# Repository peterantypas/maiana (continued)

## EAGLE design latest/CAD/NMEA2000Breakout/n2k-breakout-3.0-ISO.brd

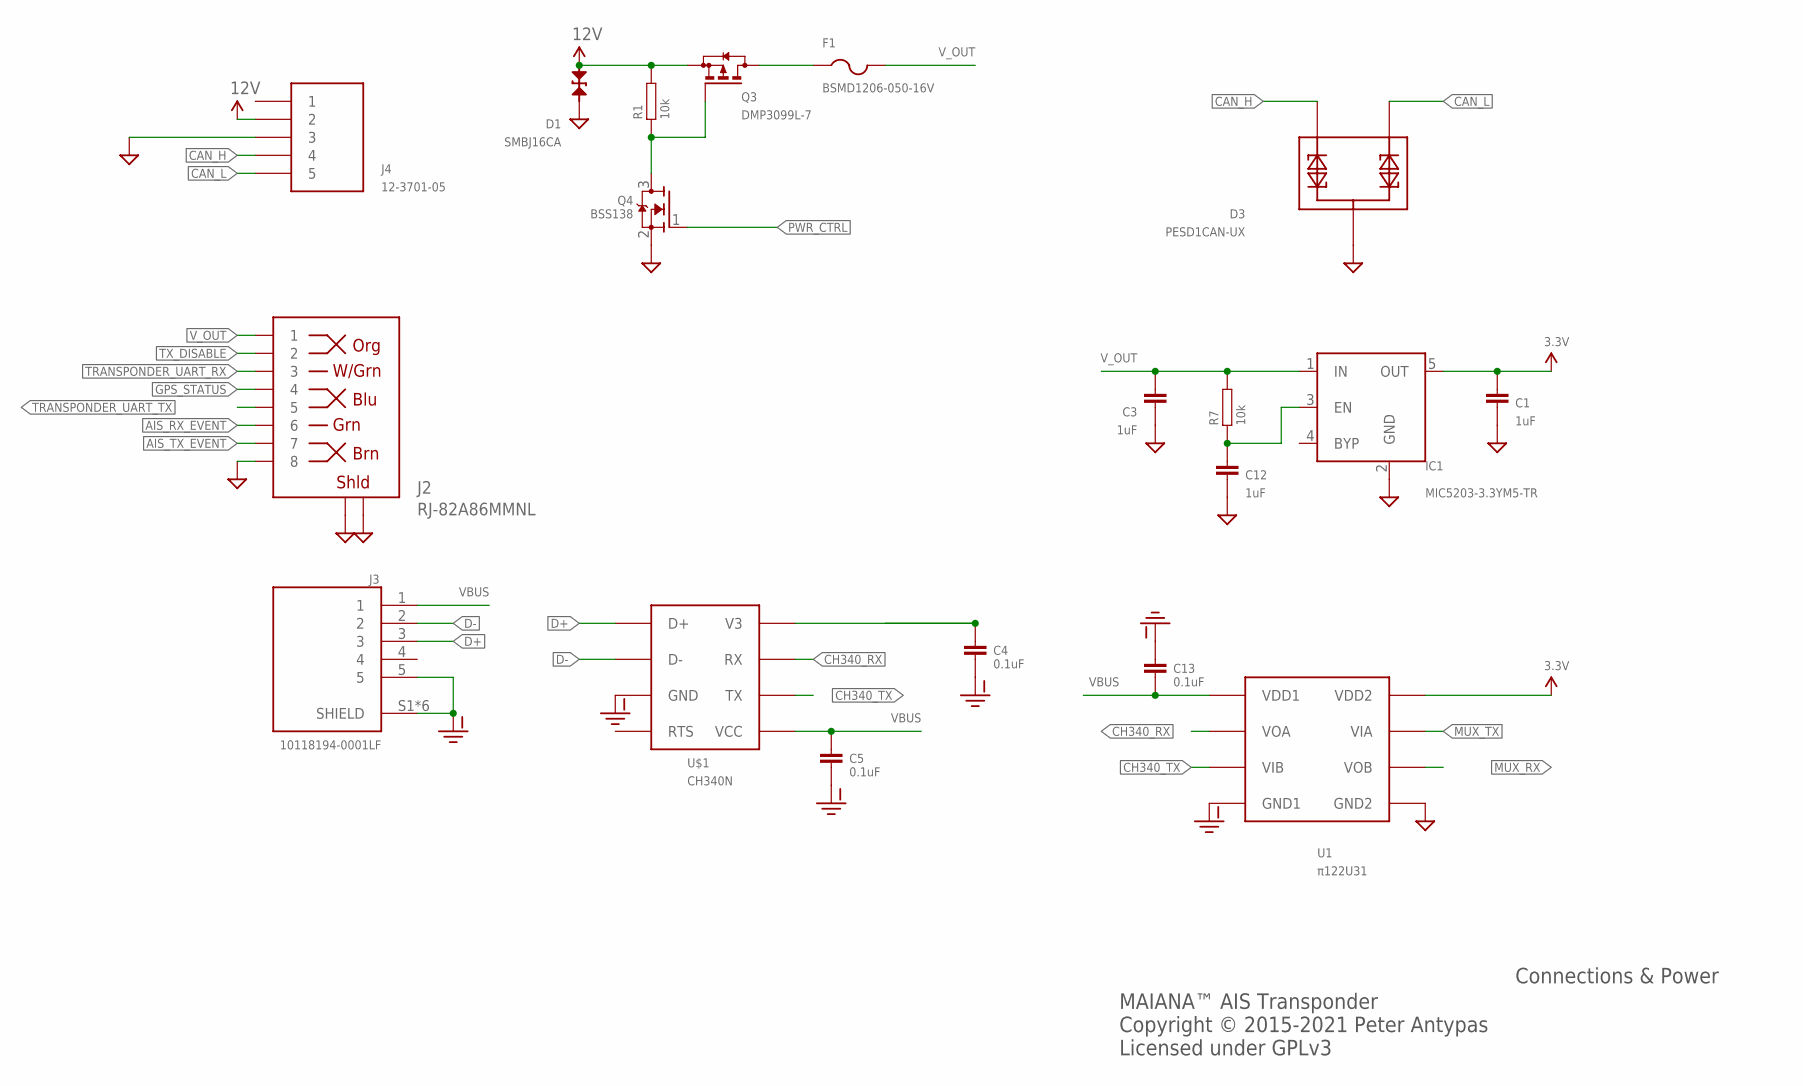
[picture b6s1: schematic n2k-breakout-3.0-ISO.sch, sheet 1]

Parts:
C1, C3, C12: 1uF; 0603
C4, C5, C13: 0.1uF; 0603
D1: SMBJ16CA; SMB-BIDIR
D3: PESD1CAN-UX; SOT65P210X110-3N
F1: BSMD1206-050-16V; R1206
IC1: MIC5203-3.3YM5-TR; SOT23-5
J2: RJ-82A86MMNL
J3: 10118194-0001LF; AMPHENOL_10118194-0001LF
J4: 12-3701-05; MICRO_C_5PIN
Q3: DMP3099L-7; SOT23
Q4: BSS138; SOT23
R1, R7: 10k; 0603
U1: π122U31; SOIC8; PARTNO π122U31
U$1: CH340N; SOIC-8; PARTNO CH340N

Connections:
3.3V: C1.P$1 (1), IC1.5 (OUT), U1.8 (VDD2); also elsewhere on the board
12V: D1.A, J4.2, Q3.2 (S), R1.P$2; also elsewhere on the board
AIS_RX_EVENT: J2.P$6 (6); also elsewhere on the board
AIS_TX_EVENT: J2.P$7 (7); also elsewhere on the board
CAN_H: D3.2, J4.4; also elsewhere on the board
CAN_L: D3.1, J4.5; also elsewhere on the board
CH340_RX: U1.2 (VOA), U$1.7 (RX)
CH340_TX: U1.3 (VIB), U$1.6 (TX)
D+: J3.3, U$1.1 (D+)
D-: J3.2, U$1.2 (D-)
GND: C1.P$2 (2), C3.P$2 (2), C12.P$2 (2), D1.C, D3.3, IC1.2 (GND), J2.P$8 (8), J2.P$9 (SHLD), J2.P$10 (SHLD), J2.P$11 (SHLD), J2.P$12 (SHLD), J4.3, Q4.2 (S), U1.5 (GND2); also elsewhere on the board
GND-ISO: C4.P$2 (2), C5.P$2 (2), C13.P$1 (1), J3.5, J3.S1 (SHIELD), J3.S2 (SHIELD), J3.S3 (SHIELD), J3.S4 (SHIELD), J3.S5 (SHIELD), J3.S6 (SHIELD), U1.4 (GND1), U$1.3 (GND)
GPS_STATUS: J2.P$4 (4); also elsewhere on the board
MUX_RX: U1.6 (VOB); also elsewhere on the board
MUX_TX: U1.7 (VIA); also elsewhere on the board
unnamed: C4.P$1 (1), U$1.8 (V3)
unnamed: Q3.1 (G), Q4.3 (D), R1.P$1
unnamed: C12.P$1 (1), IC1.3 (EN), R7.P$1
unnamed: F1.1, Q3.3 (D)
PWR_CTRL: Q4.1 (G); also elsewhere on the board
TRANSPONDER_UART_RX: J2.P$3 (3); also elsewhere on the board
TRANSPONDER_UART_TX: J2.P$5 (5); also elsewhere on the board
TX_DISABLE: J2.P$2 (2); also elsewhere on the board
VBUS: C5.P$1 (1), C13.P$2 (2), J3.1, U1.1 (VDD1), U$1.5 (VCC)
V_OUT: C3.P$1 (1), F1.2, IC1.1 (IN), J2.P$1 (1), R7.P$2

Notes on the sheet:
MAIANA™ AIS Transponder Copyright © 2015-2021 Peter Antypas Licensed under GPLv3
Connections & Power

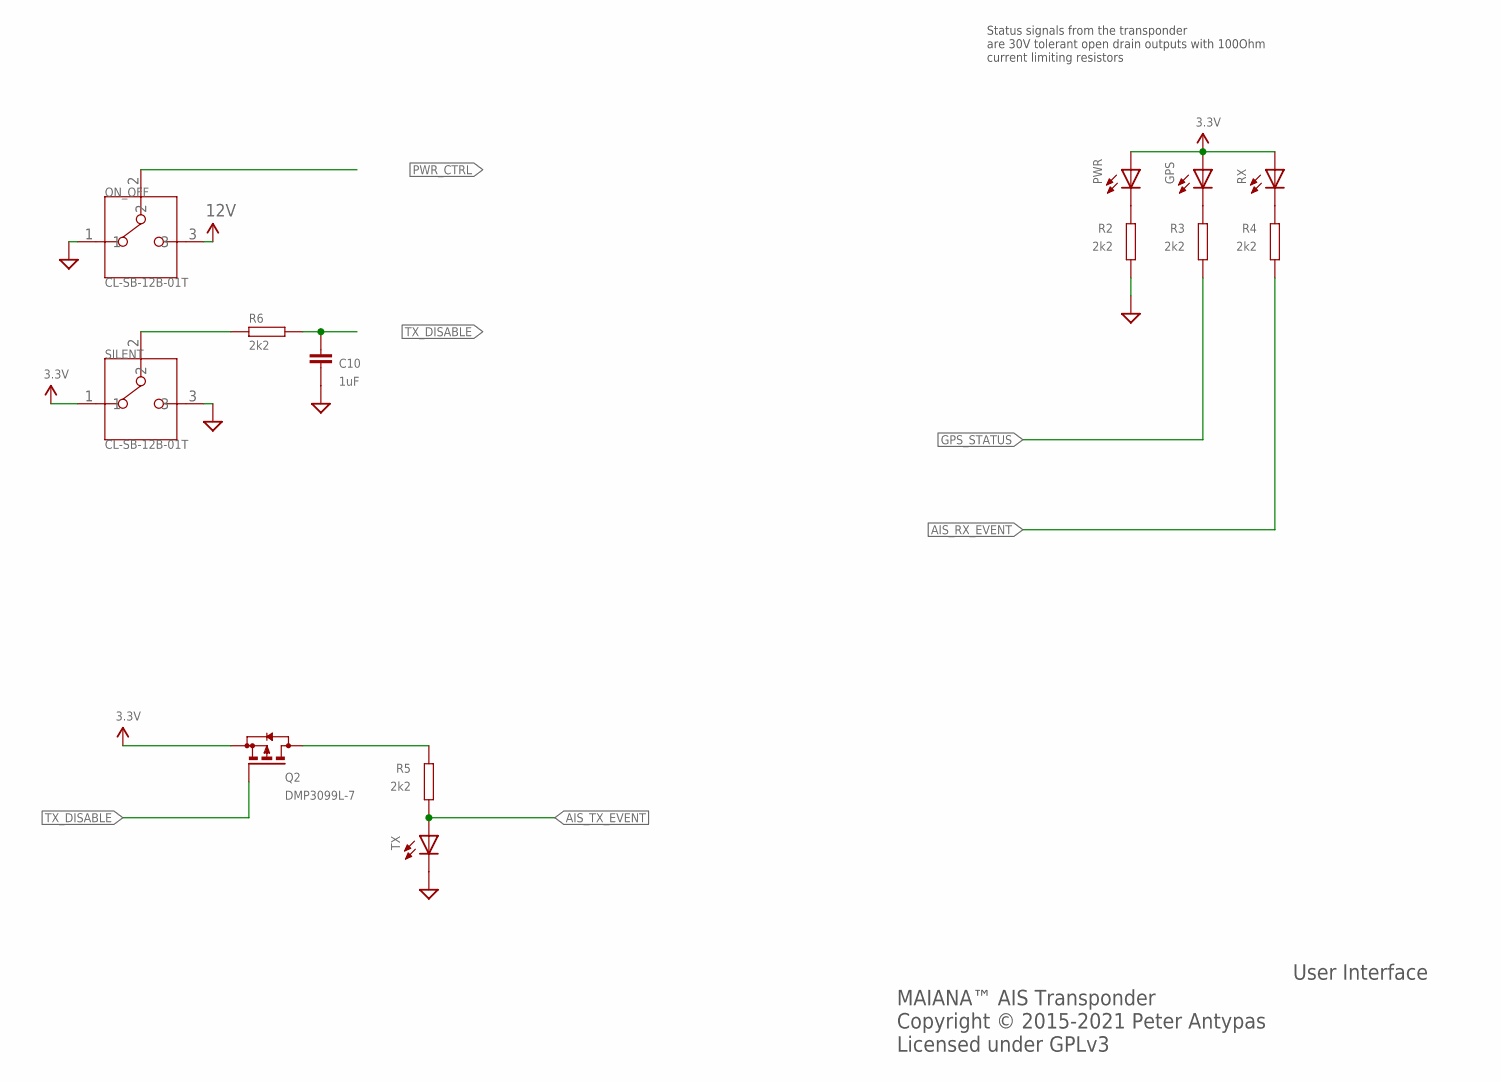
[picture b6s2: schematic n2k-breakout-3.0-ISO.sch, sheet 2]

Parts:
C10: 1uF; 0603
GPS: LEDCHIPLED_1206; CHIPLED_1206; PARTNO TJ-S3216CL9T5ALC2G-A5
ON_OFF: CL-SB-12B-01T; CL-SB-12B
PWR: LEDCHIPLED_1206; CHIPLED_1206; PARTNO TJ-S3216CL9T5ALC2G-A5
Q2: DMP3099L-7; SOT23
R2, R3, R4, R5, R6: 2k2; 0603
RX: LEDCHIPLED_1206; CHIPLED_1206; PARTNO TJ-S3216CL9T5ALC2G-A5
SILENT: CL-SB-12B-01T; CL-SB-12B
TX: LEDCHIPLED_1206; CHIPLED_1206; PARTNO TJ-S3216CL9T5ALC2G-A5

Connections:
3.3V: GPS.A, PWR.A, Q2.2 (S), RX.A, SILENT.1; also elsewhere on the board
12V: ON_OFF.3; also elsewhere on the board
AIS_RX_EVENT: R4.P$2; also elsewhere on the board
AIS_TX_EVENT: R5.P$2, TX.A; also elsewhere on the board
GND: C10.P$2 (2), ON_OFF.1, R2.P$2, SILENT.3, TX.C; also elsewhere on the board
GPS_STATUS: R3.P$2; also elsewhere on the board
unnamed: PWR.C, R2.P$1
unnamed: GPS.C, R3.P$1
unnamed: R4.P$1, RX.C
unnamed: R6.P$1, SILENT.2
unnamed: Q2.3 (D), R5.P$1
PWR_CTRL: ON_OFF.2; also elsewhere on the board
TX_DISABLE: C10.P$1 (1), Q2.1 (G), R6.P$2; also elsewhere on the board

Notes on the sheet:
Status signals from the transponder are 30V tolerant open drain outputs with 100Ohm current limiting resistors
MAIANA™ AIS Transponder Copyright © 2015-2021 Peter Antypas Licensed under GPLv3
User Interface

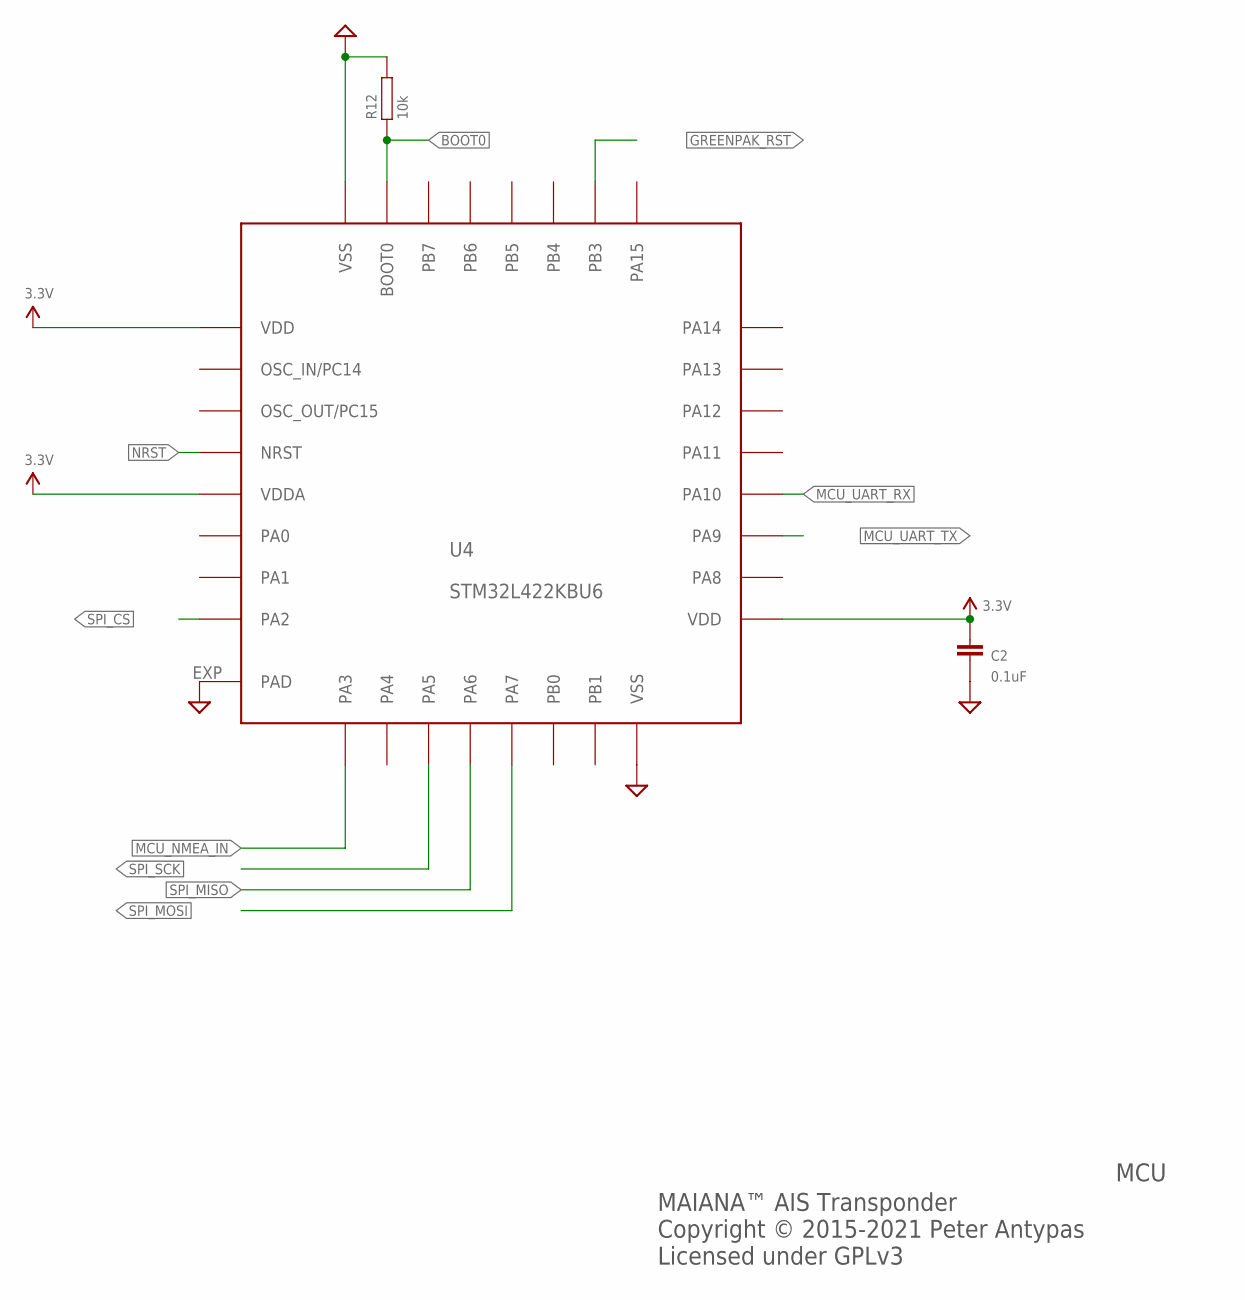
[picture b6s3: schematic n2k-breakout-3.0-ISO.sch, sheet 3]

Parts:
C2: 0.1uF; 0603
R12: 10k; 0603
U4: STM32L422KBU6; QFN32

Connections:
3.3V: C2.P$1 (1), U4.1 (VDD), U4.5 (VDDA), U4.17 (VDD); also elsewhere on the board
BOOT0: R12.P$1, U4.31 (BOOT0); also elsewhere on the board
GND: C2.P$2 (2), R12.P$2, U4.16 (VSS), U4.32 (VSS), U4.EXP (PAD); also elsewhere on the board
GREENPAK_RST: U4.26 (PB3); also elsewhere on the board
MCU_NMEA_IN: U4.9 (PA3); also elsewhere on the board
MCU_UART_RX: U4.20 (PA10); also elsewhere on the board
MCU_UART_TX: U4.19 (PA9); also elsewhere on the board
NRST: U4.4 (NRST); also elsewhere on the board
SPI_CS: U4.8 (PA2); also elsewhere on the board
SPI_MISO: U4.12 (PA6); also elsewhere on the board
SPI_MOSI: U4.13 (PA7); also elsewhere on the board
SPI_SCK: U4.11 (PA5); also elsewhere on the board

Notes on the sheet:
MAIANA™ AIS Transponder Copyright © 2015-2021 Peter Antypas Licensed under GPLv3
MCU

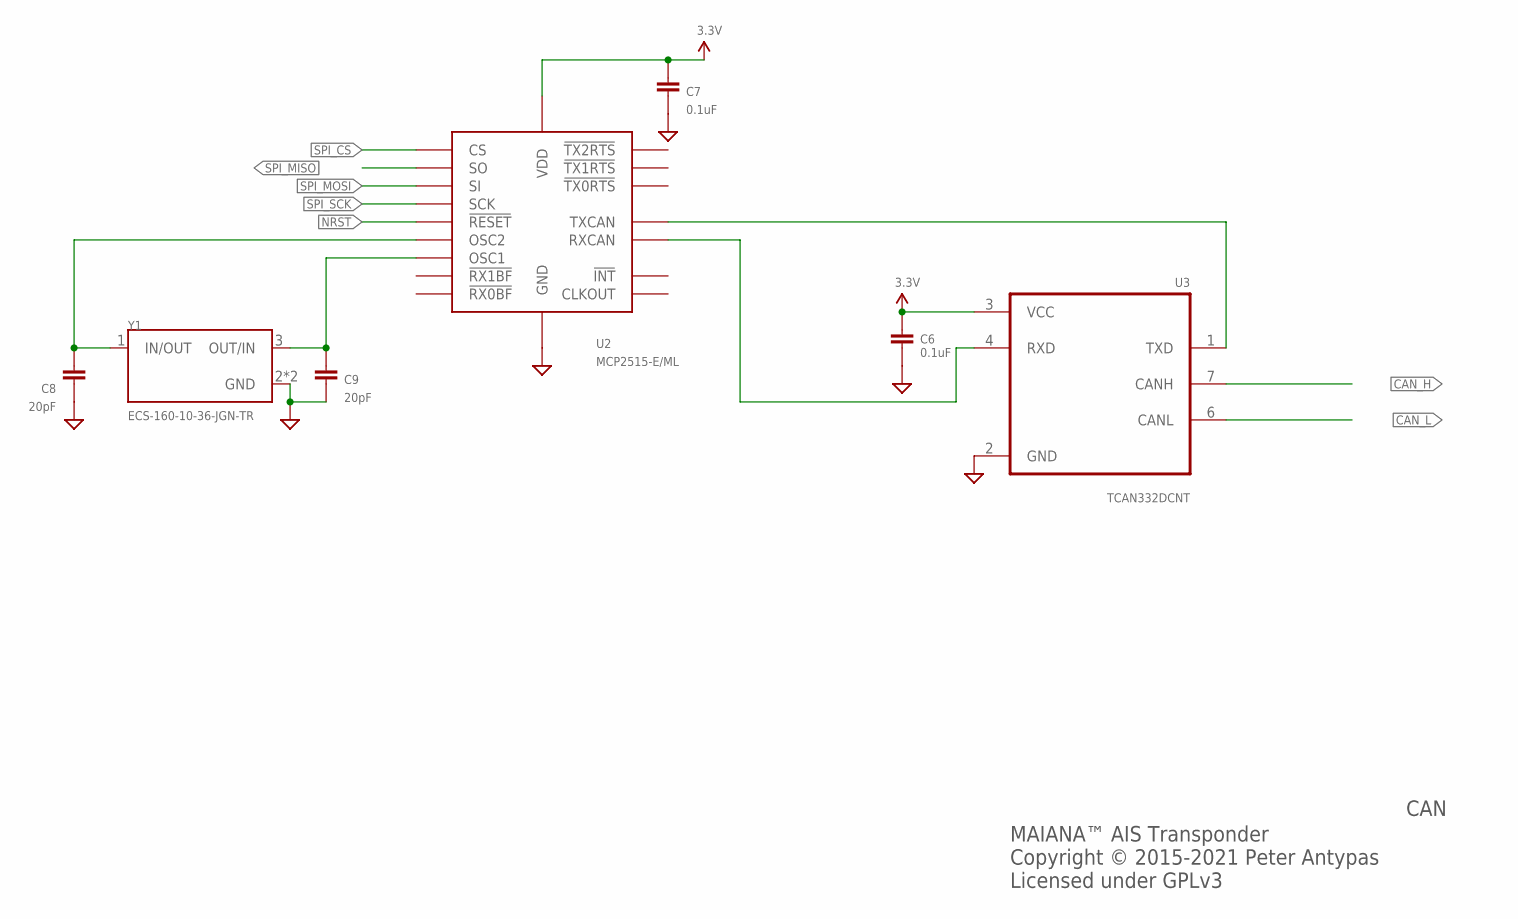
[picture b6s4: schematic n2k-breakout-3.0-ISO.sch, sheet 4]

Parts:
C6, C7: 0.1uF; 0603
C8, C9: 20pF; 0603
U2: MCP2515-E/ML; QFN20-4X4
U3: TCAN332DCNT; SOT65P280X145-8N; PARTNO TCAN332DCNT
Y1: ECS-160-10-36-JGN-TR; XTAL_ECS-160-10-36-JGN-TR

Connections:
3.3V: C6.P$1 (1), C7.P$1 (1), U2.18 (VDD), U3.3 (VCC); also elsewhere on the board
CAN_H: U3.7 (CANH); also elsewhere on the board
CAN_L: U3.6 (CANL); also elsewhere on the board
GND: C6.P$2 (2), C7.P$2 (2), C8.P$2 (2), C9.P$2 (2), U2.8 (GND), U2.EXP (GND), U3.2 (GND), Y1.2 (GND), Y1.4 (GND); also elsewhere on the board
unnamed: U2.20 (RXCAN), U3.4 (RXD)
unnamed: U2.19 (TXCAN), U3.1 (TXD)
unnamed: C9.P$1 (1), U2.7 (OSC1), Y1.3 (OUT/IN)
unnamed: C8.P$1 (1), U2.6 (OSC2), Y1.1 (IN/OUT)
NRST: U2.17 (!RESET); also elsewhere on the board
SPI_CS: U2.16 (CS); also elsewhere on the board
SPI_MISO: U2.15 (SO); also elsewhere on the board
SPI_MOSI: U2.14 (SI); also elsewhere on the board
SPI_SCK: U2.12 (SCK); also elsewhere on the board

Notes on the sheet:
MAIANA™ AIS Transponder Copyright © 2015-2021 Peter Antypas Licensed under GPLv3
CAN

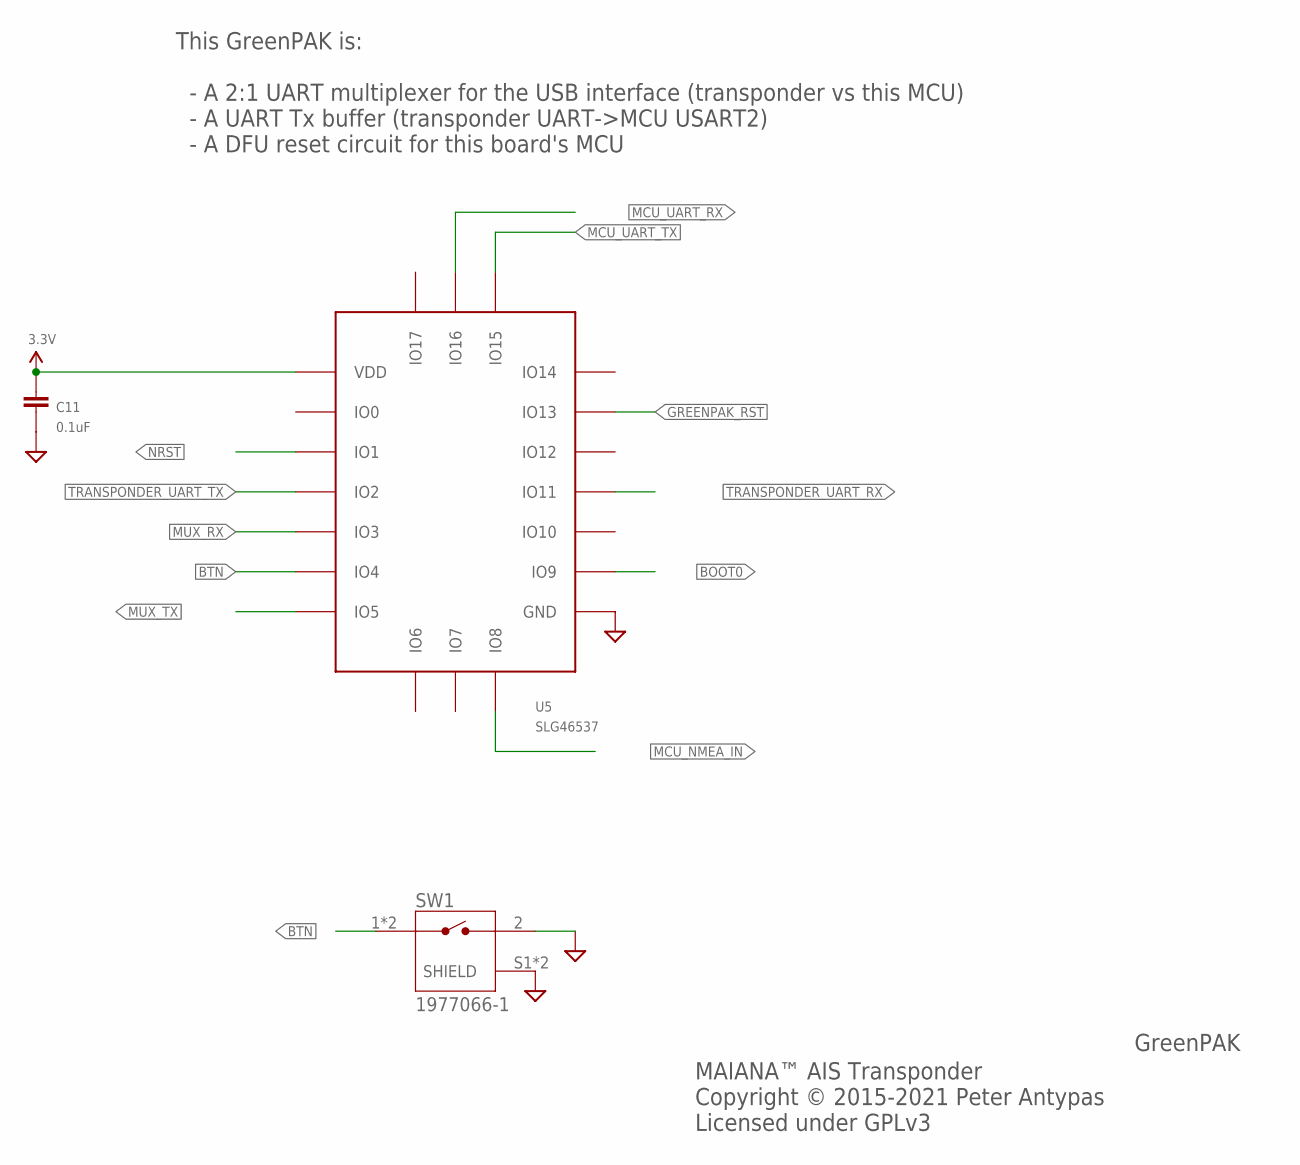
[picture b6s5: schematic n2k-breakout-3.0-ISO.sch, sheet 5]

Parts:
C11: 0.1uF; 0603
SW1: 1977066-1; TE_1977066-1
U5: SLG46537; STQFN20L

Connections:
3.3V: C11.P$1 (1), U5.P$1 (VDD); also elsewhere on the board
BOOT0: U5.P$12 (IO9); also elsewhere on the board
BTN: SW1.1, SW1.3 (1), U5.P$6 (IO4)
GND: C11.P$2 (2), SW1.2, SW1.S1 (SHIELD), SW1.S2 (SHIELD), U5.P$11 (GND); also elsewhere on the board
GREENPAK_RST: U5.P$16 (IO13); also elsewhere on the board
MCU_NMEA_IN: U5.P$10 (IO8); also elsewhere on the board
MCU_UART_RX: U5.P$19 (IO16); also elsewhere on the board
MCU_UART_TX: U5.P$18 (IO15); also elsewhere on the board
MUX_RX: U5.P$5 (IO3); also elsewhere on the board
MUX_TX: U5.P$7 (IO5); also elsewhere on the board
NRST: U5.P$3 (IO1); also elsewhere on the board
TRANSPONDER_UART_RX: U5.P$14 (IO11); also elsewhere on the board
TRANSPONDER_UART_TX: U5.P$4 (IO2); also elsewhere on the board

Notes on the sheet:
This GreenPAK is: - A 2:1 UART multiplexer for the USB interface (transponder vs this MCU) - A UART Tx buffer (transponder UART->MCU USART2) - A DFU reset circuit for this board's MCU
MAIANA™ AIS Transponder Copyright © 2015-2021 Peter Antypas Licensed under GPLv3
GreenPAK

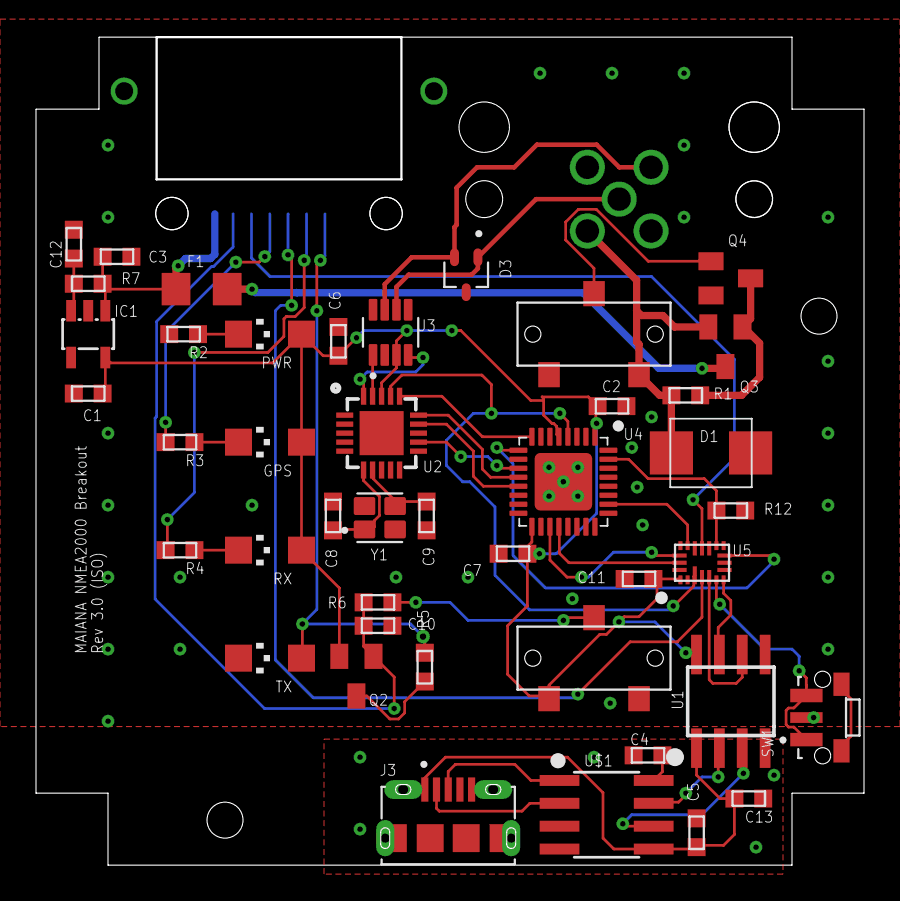
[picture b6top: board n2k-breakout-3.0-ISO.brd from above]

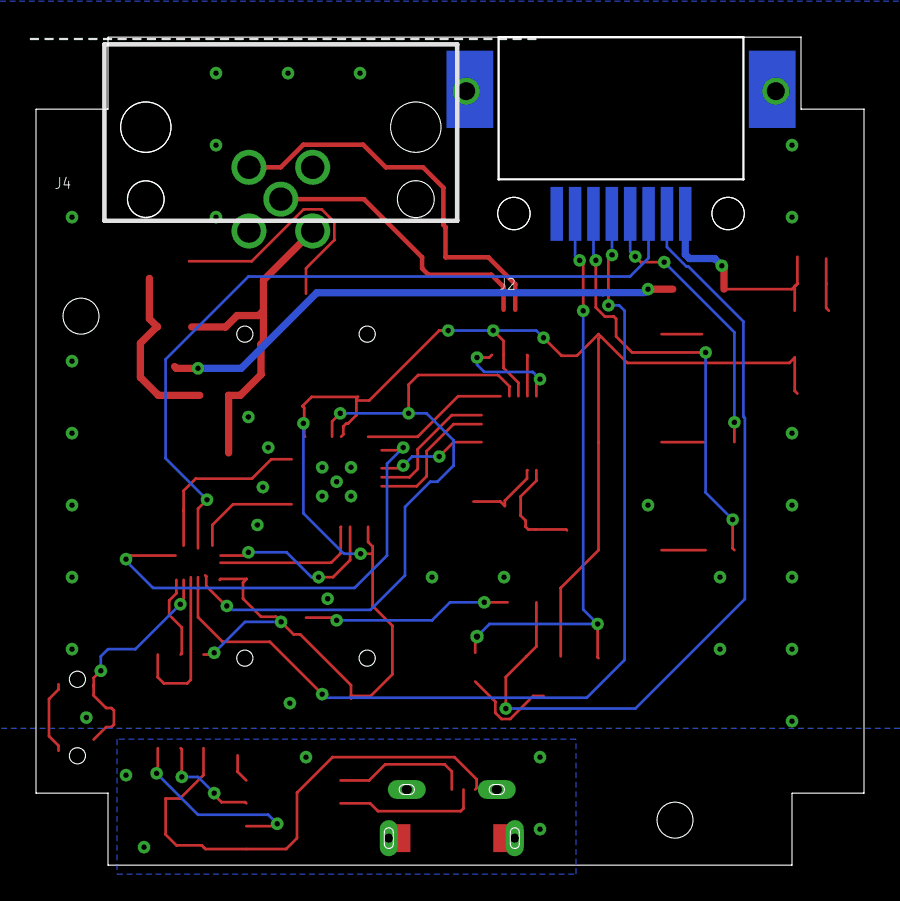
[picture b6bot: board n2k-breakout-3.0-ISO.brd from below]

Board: 2 copper layers, 45.9 x 45.9 mm, 45 parts (2 on the bottom side), 45 nets.

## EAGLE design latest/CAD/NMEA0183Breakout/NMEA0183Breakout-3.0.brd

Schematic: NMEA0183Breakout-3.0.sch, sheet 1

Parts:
C1, C2, C6: 1uF; 0603
D1: SMBJ16CA; SMB-BIDIR
F1: BSMD1206-050-16V; R1206
IC1: LD2985BM50R; SOT23-5
J2: RJ-82A86MMNL
JP1: OSTVN04A150; 1X04
Q1, Q3: DMP3099L-7; SOT23
Q4: BSS138; SOT23
R1, R9, R10: 10k; 0603
S1, S2: LC1258XXNP

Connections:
5V: C1.P$1 (1), IC1.5 (OUT), S2.P$3 (3); also elsewhere on the board
12V: D1.A, JP1.1, Q1.3 (D)
AIS_RX_EVENT: J2.P$6 (6); also elsewhere on the board
AIS_TX_EVENT: J2.P$7 (7); also elsewhere on the board
GND: C1.P$2 (2), C2.P$2 (2), C6.P$2 (2), D1.C, IC1.2 (GND), J2.P$8 (8), J2.P$9 (SHLD), J2.P$10 (SHLD), J2.P$11 (SHLD), J2.P$12 (SHLD), JP1.2, Q1.1 (G), Q4.2 (S), R10.P$1, S1.P$1 (1), S2.P$1 (1); also elsewhere on the board
GPS_STATUS: J2.P$4 (4); also elsewhere on the board
unnamed: R9.P$2, S2.P$2 (2)
unnamed: Q3.1 (G), Q4.3 (D), R1.P$1
unnamed: F1.1, Q3.3 (D)
PWR_CTRL: Q4.1 (G), R10.P$2, S1.P$2 (2)
S1: JP1.3; also elsewhere on the board
S2: JP1.4; also elsewhere on the board
TRANSPONDER_UART_RX: J2.P$3 (3); also elsewhere on the board
TRANSPONDER_UART_TX: J2.P$5 (5); also elsewhere on the board
TX_DISABLE: C6.P$1 (1), J2.P$2 (2), R9.P$1; also elsewhere on the board
V_IN: Q1.2 (S), Q3.2 (S), R1.P$2, S1.P$3 (3)
V_OUT: C2.P$1 (1), F1.2, IC1.1 (IN), IC1.3 (EN), J2.P$1 (1)

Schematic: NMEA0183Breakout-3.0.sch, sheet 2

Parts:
C4, C5: 0.1uF; 0603
D2: 3.3V; SOD-323
J1: 10118194-0001LF; AMPHENOL_10118194-0001LF
R8: 75R; 0603
U$1: CH340N; SOIC-8; PARTNO CH340N
U$4: SRV05-4; SOT23-6

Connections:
D+: J1.3, U$1.1 (D+), U$4.3 (IO2)
D-: J1.2, U$1.2 (D-), U$4.1 (IO1)
GND: C4.P$2 (2), C5.P$2 (2), D2.A, J1.5, J1.S1 (SHIELD), J1.S2 (SHIELD), J1.S3 (SHIELD), J1.S4 (SHIELD), J1.S5 (SHIELD), J1.S6 (SHIELD), U$1.3 (GND), U$4.2 (GND); also elsewhere on the board
unnamed: C4.P$1 (1), U$1.8 (V3)
unnamed: C5.P$1 (1), D2.C, R8.P$2, U$1.5 (VCC)
TRANSPONDER_UART_RX: U$1.6 (TX); also elsewhere on the board
TRANSPONDER_UART_TX: U$1.7 (RX); also elsewhere on the board
VBUS: J1.1, R8.P$1, U$4.5 (VCC)

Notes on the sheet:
The CH330N only works when it's bus powered, and its UART logic level is dictated by VCC. That's why we use a 3.3V Zener to regulate it.

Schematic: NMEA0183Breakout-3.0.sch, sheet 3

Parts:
GPS: LEDCHIPLED_1206; CHIPLED_1206; PARTNO TJ-S3216CL9T5ALC2G-A5
PWR: LEDCHIPLED_1206; CHIPLED_1206; PARTNO TJ-S3216CL9T5ALC2G-A5
Q2: DMP3099L-7; SOT23
R2, R3, R4, R5: 2k2; 0603
RX: LEDCHIPLED_1206; CHIPLED_1206; PARTNO TJ-S3216CL9T5ALC2G-A5
TX: LEDCHIPLED_1206; CHIPLED_1206; PARTNO TJ-S3216CL9T5ALC2G-A5

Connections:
5V: GPS.A, PWR.A, Q2.2 (S), RX.A; also elsewhere on the board
AIS_RX_EVENT: R4.P$2; also elsewhere on the board
AIS_TX_EVENT: R5.P$2, TX.A; also elsewhere on the board
GND: R2.P$2, TX.C; also elsewhere on the board
GPS_STATUS: R3.P$2; also elsewhere on the board
unnamed: PWR.C, R2.P$1
unnamed: GPS.C, R3.P$1
unnamed: R4.P$1, RX.C
unnamed: Q2.3 (D), R5.P$1
TX_DISABLE: Q2.1 (G); also elsewhere on the board

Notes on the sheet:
Status signals from the transponder are 30V tolerant open drain outputs with 100Ohm current limiting resistors

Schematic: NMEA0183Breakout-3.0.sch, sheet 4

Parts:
C3: 0.1uF; 0603
R6, R7: 0R; 0603
U1: DS8921M; SOIC127P599X175-8N

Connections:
5V: C3.P$1 (1), U1.1 (VCC); also elsewhere on the board
GND: C3.P$2 (2), U1.4 (GND); also elsewhere on the board
S1: R7.P$2, U1.5 (DO-); also elsewhere on the board
S2: R6.P$2, U1.6 (DO+); also elsewhere on the board
TRANSPONDER_UART_RX: R7.P$1; also elsewhere on the board
TRANSPONDER_UART_TX: R6.P$1, U1.3 (DI); also elsewhere on the board

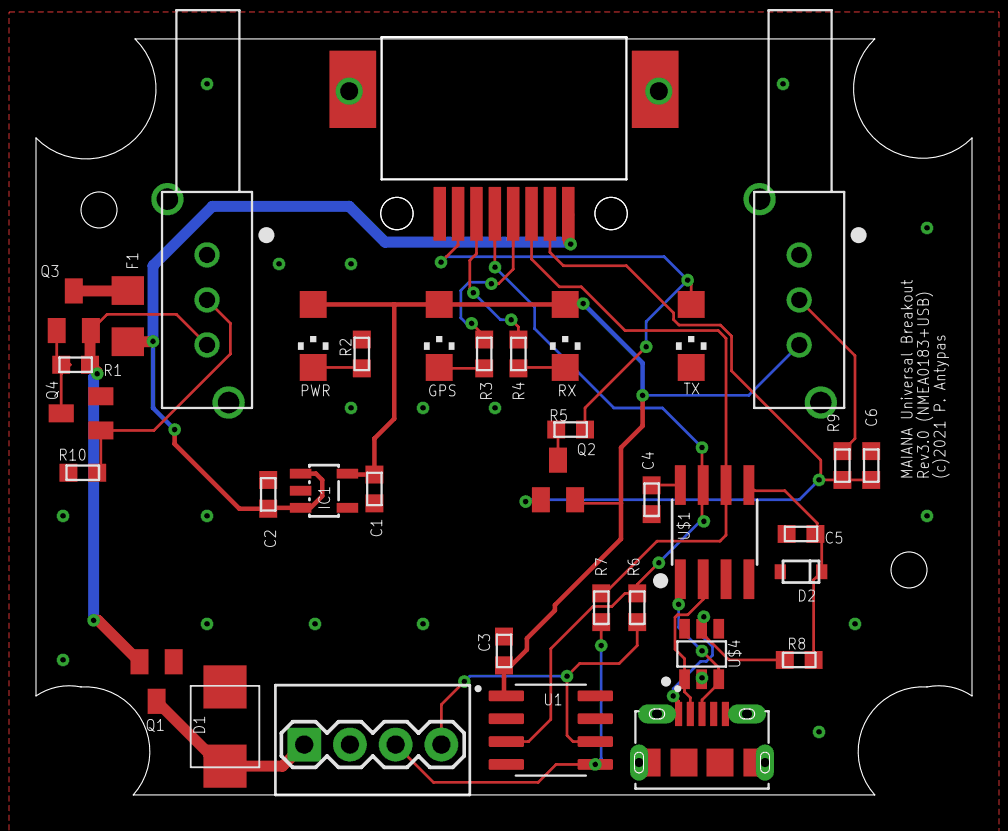
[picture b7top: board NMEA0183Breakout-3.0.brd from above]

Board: 2 copper layers, 51.9 x 42.0 mm, 36 parts (0 on the bottom side), 26 nets.

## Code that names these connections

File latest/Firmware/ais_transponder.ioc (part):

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Mcu.Name=STM32L432K(B-C)Ux
Mcu.Package=UFQFPN32
Mcu.UserName=STM32L432KBUx
PA0-CK_IN.Signal=GPIO_Output
PA1.Signal=GPIO_Input
PA10.GPIOParameters=GPIO_Speed
PA10.GPIO_Speed=GPIO_SPEED_FREQ_MEDIUM
PA10.Mode=Asynchronous
PA10.Signal=USART1_RX
PA11.Signal=GPIO_Input
PA13\ (JTMS-SWDIO).Mode=Serial_Wire
PA13\ (JTMS-SWDIO).Signal=SYS_JTMS-SWDIO
PA14\ (JTCK-SWCLK).Mode=Serial_Wire
PA14\ (JTCK-SWCLK).Signal=SYS_JTCK-SWCLK
PA15\ (JTDI).Signal=GPIO_Output
PA2.GPIOParameters=GPIO_ModeDefaultEXTI
PA2.GPIO_ModeDefaultEXTI=GPIO_MODE_IT_RISING_FALLING
PA2.Signal=GPXTI2
PA3.Signal=USART2_RX
PA4.Signal=GPIO_Output
PA5.Mode=Full_Duplex_Master
PA5.Signal=SPI1_SCK
PA6.Mode=Full_Duplex_Master
PA6.Signal=SPI1_MISO
PA7.Mode=Full_Duplex_Master
PA7.Signal=SPI1_MOSI
PA8.Signal=GPIO_Input
PA9.GPIOParameters=GPIO_Speed
PA9.GPIO_Speed=GPIO_SPEED_FREQ_MEDIUM
PA9.Mode=Asynchronous
PA9.Signal=USART1_TX
PB0.Signal=GPIO_Output
PB1.Signal=GPIO_Input
PB3\ (JTDO-TRACESWO).Signal=GPIO_Input
PB4\ (NJTRST).Signal=GPIO_Input
PC14-OSC32_IN\ (PC14).Signal=GPIO_Output
PC15-OSC32_OUT\ (PC15).Signal=GPIO_Output
RCC.HSE_VALUE=8000000
RCC.SYSCLKFreq_VALUE=80000000
RCC.SYSCLKSource=RCC_SYSCLKSOURCE_PLLCLK
board=ais_transponder

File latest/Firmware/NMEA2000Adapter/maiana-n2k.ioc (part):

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Mcu.Name=STM32L422KBUx
Mcu.Package=UFQFPN32
Mcu.UserName=STM32L422KBUx
PA10.Mode=Asynchronous
PA10.Signal=USART1_RX
PA13\ (JTMS/SWDIO).Mode=Serial_Wire
PA13\ (JTMS/SWDIO).Signal=SYS_JTMS-SWDIO
PA14\ (JTCK/SWCLK).Mode=Serial_Wire
PA14\ (JTCK/SWCLK).Signal=SYS_JTCK-SWCLK
PA2.GPIOParameters=PinState,GPIO_Label,GPIO_ModeDefaultOutputPP
PA2.GPIO_Label=SPI1_CS
PA2.GPIO_ModeDefaultOutputPP=GPIO_MODE_OUTPUT_PP
PA2.PinState=GPIO_PIN_SET
PA2.Signal=GPIO_Output
PA4.GPIOParameters=PinState,GPIO_Label,GPIO_ModeDefaultOutputPP
PA4.GPIO_Label=CAN_RST
PA4.GPIO_ModeDefaultOutputPP=GPIO_MODE_OUTPUT_OD
PA4.PinState=GPIO_PIN_SET
PA4.Signal=GPIO_Output
PA5.Mode=Full_Duplex_Master
PA5.Signal=SPI1_SCK
PA6.Mode=Full_Duplex_Master
PA6.Signal=SPI1_MISO
PA7.Mode=Full_Duplex_Master
PA7.Signal=SPI1_MOSI
PA9.Mode=Asynchronous
PA9.Signal=USART1_TX
PB0.Signal=GPXTI0
PB6.Mode=I2C
PB6.Signal=I2C1_SCL
PB7.Mode=I2C
PB7.Signal=I2C1_SDA
RCC.HSE_VALUE=8000000
RCC.SYSCLKFreq_VALUE=80000000
RCC.SYSCLKSource=RCC_SYSCLKSOURCE_PLLCLK
board=custom

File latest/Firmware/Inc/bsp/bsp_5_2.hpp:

/*
  Copyright (c) 2016-2020 Peter Antypas

  This file is part of the MAIANA™ transponder firmware.

  The firmware is free software: you can redistribute it and/or modify
  it under the terms of the GNU General Public License as published by
  the Free Software Foundation, either version 3 of the License, or
  (at your option) any later version.

  This program is distributed in the hope that it will be useful,
  but WITHOUT ANY WARRANTY; without even the implied warranty of
  MERCHANTABILITY or FITNESS FOR A PARTICULAR PURPOSE.  See the
  GNU General Public License for more details.

  You should have received a copy of the GNU General Public License
  along with this program.  If not, see <https://www.gnu.org/licenses/>
*/

#ifndef INC_BSP_5_2_HPP_
#define INC_BSP_5_2_HPP_


// GPIO Pin definitions
#define RFSW_CTRL_PORT            GPIOC
#define RFSW_CTRL_PIN             GPIO_PIN_14

#define EEPROM_WREN_PORT          GPIOC
#define EEPROM_WREN_PIN           GPIO_PIN_15

#define CS2_PORT                  GPIOA
#define CS2_PIN                   GPIO_PIN_0

#define TRX_IC_CLK_PORT           GPIOA
#define TRX_IC_CLK_PIN            GPIO_PIN_1

#define GNSS_1PPS_PORT            GPIOA
#define GNSS_1PPS_PIN             GPIO_PIN_2

#define GNSS_NMEA_RX_PORT         GPIOA
#define GNSS_NMEA_RX_PIN          GPIO_PIN_3

#define CS1_PORT                  GPIOA
#define CS1_PIN                   GPIO_PIN_4

#define SCK_PORT                  GPIOA
#define SCK_PIN                   GPIO_PIN_5

#define MISO_PORT                 GPIOA
#define MISO_PIN                  GPIO_PIN_6

#define MOSI_PORT                 GPIOA
#define MOSI_PIN                  GPIO_PIN_7

#define SDN1_PORT                 GPIOB
#define SDN1_PIN                  GPIO_PIN_0

#define TRX_IC_DATA_PORT          GPIOB
#define TRX_IC_DATA_PIN           GPIO_PIN_1

#define DFU_EN_PORT               GPIOA
#define DFU_EN_PIN                GPIO_PIN_8

#define UART_TX_PORT              GPIOA
#define UART_TX_PIN               GPIO_PIN_9

#define UART_RX_PORT              GPIOA
#define UART_RX_PIN               GPIO_PIN_10

#define SDN2_PORT                 GPIOA
#define SDN2_PIN                  GPIO_PIN_15

#define RX_IC_CLK_PORT            GPIOB
#define RX_IC_CLK_PIN             GPIO_PIN_3

#define RX_IC_DATA_PORT           GPIOB
#define RX_IC_DATA_PIN            GPIO_PIN_4

#define PA_BIAS_PORT              GPIOB
#define PA_BIAS_PIN               GPIO_PIN_5

#define I2C_SCL_PORT              GPIOB
#define I2C_SCL_PIN               GPIO_PIN_6

#define I2C_SDA_PORT              GPIOB
#define I2C_SDA_PIN               GPIO_PIN_7


#endif /* INC_BSP_5_2_HPP_ */

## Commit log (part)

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2020-10-03 Image
2020-10-03 License
2020-10-03 Photo2
2020-10-03 Initial commit / transfer from bitbucket
2020-10-03 Initial code commit
2020-10-03 Added Eagle CAD files
2020-10-03 Cleanup
2020-10-03 Schematic for 5.2
2020-10-03 Schematic for 6.1
2020-10-03 README tweak
2020-10-03 Switched default build to board 6.x
2020-10-03 Board 6.1.1
2020-10-03 README for Python script
2020-10-03 README in Firmware/
2020-10-03 More README
2020-10-04 Gerbers
2020-10-06 Build support for L412 (untested)
2020-10-07 Board 6.2.0
2020-10-07 Proper support for L412 MCU
2020-10-07 Comments in schematic
2020-10-08 README again
2020-10-08 Tweaked
2020-10-08 Board 6.2 tweak
2020-10-08 Transceiver tweak
2020-10-08 Checkpoint
2020-10-08 Memory overflow bug
2020-10-09 FUBAR
2020-10-09 First running port
2020-10-09 Watchdog
2020-10-10 Removed board 6.2
2020-10-13 Broken
2020-10-13 Board 6.1.0 bringup
2020-10-13 TX_OFF switch works now
2020-10-13 DFU logic moved to BSP
2020-10-17 RJ45 Breakout
2020-10-17 Removed 6.2
2020-10-17 Gerbers and schematic for breakout
2020-10-18 Tentatively adding board 7.0.x
2020-10-18 README
2020-10-18 7.x gerbers
2020-10-18 7.x assembly variants
2020-10-18 Updated photo
2020-10-19 Introduced 'blink' BSP functions
2020-10-19 BSP backward compatibility
2020-10-19 Removing Board 4.3
2020-10-23 Removed unused events
2020-10-23 Removed obsolete code
2020-11-02 Hard-coded noise floor for now
2020-11-02 Checkpoint before changing NF detection
2020-11-02 Overhaul of NF detector
2020-11-02 Corrected IRQ priorities
2020-11-02 Working, push is 4x faster
2020-11-02 No profiling
2020-11-03 RXPacket pool
2020-11-03 Profiling
2020-11-03 Validated good RX performance
2020-11-03 Checkpoint. Best RX performance possible with current architecture
2020-11-03 Removed profiling
2020-11-03 Reduced RSSI sampling to improve RX yield
2020-11-04 Checkpoint before changing START_RX implementation
2020-11-04 onBitClock() rarely runs over 104us now
2020-11-04 Good enough
2020-11-04 That wasn't a bare metal build :(
2020-11-04 Minor optimization
2020-11-21 Board 9.3
2020-11-21 Board 9.3 CAD
2020-11-21 9.3 photo
2020-11-25 Build issue w/ different SDKs
2020-11-30 More photos
2020-12-05 Corrected some transmitted fields
2020-12-11 Starting work on Si4362
2020-12-11 Appears to be detecting Si4463
2020-12-12 BSP for 10.x
2020-12-12 Fixed huge bug in command processor
2020-12-13 Board 10.x
2020-12-13 Board 10
2020-12-13 Introduced 'quiet' CLI mode for programming station data
2020-12-14 Flash persistence
2020-12-14 Removed FreeRTOS
2020-12-21 Crude, but working
2020-12-21 Chip-specific config headers
2020-12-25 Restored original CCA headroom, fixed GPIO config for RX IC
2020-12-25 Missing include
2020-12-25 Fixed message 24 encoding bug
2020-12-25 Deployed to boat
2020-12-25 Ejecting language.settings.xml from git
2020-12-25 Board 10.0.1
2020-12-25 10.0.1 schematic
2020-12-25 10.0.1 gerber update
2020-12-26 BSP cleanup
2020-12-27 Minor cleanup
2021-01-30 Fixed issue #46
2021-02-26 Resetting MCU every hour
2021-03-09 Untested support for STM32L422xx
2021-03-20 config and bsp for 10.5.0
2021-03-30 Board 10.5
2021-04-30 BSP 10.5
2021-05-05 L422 + gitignore
2021-05-24 Support for board 10.5/6 and 10.7
2021-05-31 BSP fixes
2021-06-01 Board 10.5.x CAD files
2021-06-05 10.5.0 BOM
2021-06-05 BSP cleanup + LEDManager
2021-06-27 Board 10.9 bringup
2021-07-10 Board 10.9 Finished
2021-07-11 Updated CAD
2021-07-11 More CAD
2021-07-11 Fill bits was incorrectly set to 0 on all single frame messages
2021-07-24 Project cleanup
2021-07-30 Project restructuring
2021-07-30 Placeholder
2021-07-30 NMEA 2000 Adapter FW
2021-07-30 FreeCAD for 0183 box
2021-08-04 N2K breakout final
2021-08-06 Manuals
2021-08-21 BSP for board 11.0
2021-08-24 Board 11.0 bringup complete
2021-08-27 GNSS should be off by default
2021-08-27 Board 11.0 final
2021-08-29 Enabled watchdog for N2k adapter
2021-09-09 Renamed folder
2021-09-20 Updated manuals
2021-09-20 Manual correction
2021-09-23 Initial changes for OP
2021-09-23 sentence
2021-09-23 TX LED logic 100% in FW
2021-09-27 OpenPlotter commands
2021-09-28 Small optimizations
2021-10-04 Legacy breakout support
2021-10-04 Cherry picked support for new/legacy breakouts
2021-10-04 Better way to mange TX LED
2021-10-12 Persistence delegated to BSP again
2021-10-12 Preliminary support for i2c EEPROM
2021-10-12 Migrate from flash to EEPROM
2021-10-13 Correct noise floor limit
2021-10-20 Board 11.3.0 is it
2021-10-20 FW rev 3.3.0
2021-10-20 Board 11.3 & UART breakout
2021-10-20 UART breakout photo
2021-10-23 Improved RX for Si4463
2021-10-25 New manuals
2021-10-29 GPS LED wasn't turning off after loss of fix
2021-11-03 Correction for Issue #88
2021-11-09 Increased robustness of FW update
2021-11-11 L432 build
2021-11-11 Build flags for L432
2021-11-12 New system information fields in
2021-11-12 Fixed huge regression bug
2021-11-12 v3.3.3
2021-11-13 FW update manual
2021-11-15 Brought back an old bootloader from the cold
2021-11-15 Bootloader-compatible build variants
2021-11-15 Bootloader flashes LEDs
2021-11-15 Release 4.0.0
2021-11-17 Python3 script for new bootloader
2021-11-17 Update README.md
    README update
2021-11-19 N2K adapter schematic
2021-11-19 N2K adapter gerbers
2021-11-19 N2K adapter Eagle files
2021-11-29 Fixed backward compatibility bug with legacy bootloader
2021-12-03 Delete system.tmp
    Deleted .tmp file
2021-12-03 Delete license.tmp
    Deleted .tmp file
2021-12-08 Updated USB breakout CAD
2021-12-08 Updated NMEA0183 breakout
2021-12-28 New UART+USB breakout
2021-12-28 Antenna parts
2021-12-28 Board 11.5.2
2021-12-28 Adapter image
2021-12-31 Add files via upload
    Fixed manual
2022-01-28 Checkpoint 2
2022-01-30 Improved robustness
2022-01-30 Fully functional but needs a lot of hardening
2022-01-30 Can detect DFU mode upon connecting
2022-02-03 Alpha version of WX app
2022-02-11 Fixed BSP for board 11.0
2022-02-12 New N2K adapter board
2022-02-14 GUI client validating HW revision
2022-02-20 align labels right
2022-02-21 New label alignment
2022-02-21 Fixed MAIANA Python client for Mac OS
2022-02-22 fixes for sizing and alignment
2022-02-24 Retuning for ECS crystal
2022-02-24 Fixed UI to enable FW update when board boots in 'rescue' mode
2022-02-24 Retuned for ECS crystal
2022-02-24 Another GUI bugfix
2022-02-24 GUI version 3.0
2022-02-24 GUI version 0.3
2022-03-01 .gitignore
2022-03-01 Binaries
2022-03-11 Board 7
2022-04-28 Latest n2k adapter CAD
2022-05-10 Board 11.8.0
2022-06-28 L432 support in N2K adapter
2022-12-03 Initial check-in for WiFi adapter
2022-12-04 Initial web server
2022-12-04 Main web page done
2022-12-04 Added all core pages
2022-12-05 Cleaned up http handlers
2022-12-05 Refactored HTTP handlers
2022-12-06 First functioning form
2022-12-06 Button reset logic
2022-12-07 NMEA gateway configuration
2022-12-07 Refactored CSS
2022-12-07 Refactoring and NMEA gateway skeleton
2022-12-08 Successful basic TCP server
2022-12-11 UDP sender
2022-12-11 WiFi station config works
2022-12-11 WiFi rollback, auto reboot on update
2022-12-11 NMEA gateway mode changes immediately
2022-12-12 AIS form retrieves data
2022-12-12 AIS configuration working
2022-12-13 Displaying HW and FW revs on main page
2023-01-16 Adding sdkconfig
2023-01-17 Factory reset
2023-03-01 Support for 10.0.1
    Regression for support of latest software on board 10.0.1
    Essentially it boils down to sense of the GPS_EN line and RX_EN line
2023-03-11 Fixed GPIO handling
2023-04-25 Abandoning for now
2023-04-29 Fixed some builds
2023-05-03 Abandoning
2023-06-19 Leaving this branch alone
2023-09-10 Updated installation manual
2023-09-13 Added bootloader binaries
2023-09-27 Detecting RF IC initialization error
2024-01-25 Board 11.9.0
2024-02-03 Board 11.9.1
2024-02-13 Initial build for 64K flash
2024-02-16 First build with L412 on 11.8.0
2024-02-16 New binaries
2024-02-17 Removed 11.9.0
2024-03-11 Initial testing of XO trimming CLI
2024-03-11 4.4.0
2024-03-11 Removed build directory
2024-03-11 Added 4.4.0 binary
2024-04-01 Fixed MCU reporting in CLI
2024-04-01 Added 4.4.1 binary
2024-06-15 Added 4.4.1 binary for L432 boards
2024-11-20 Reset '1' count after bitstuffing.
2025-01-29 KiCad projects for N2K and 0183 adapters
2025-07-09 Fixed build under GCC 13+
2026-04-29 feat: optional external GPS via USART1 (extgps on/off)
    Adds an opt-in feature that lets the transponder source GPS NMEA from
    the host USART1 (Signal K, chartplotter, multiplexer) instead of the
    internal u-blox module. Useful when the AIS unit is mounted in a
    location with poor sky visibility for the internal GPS.
    Default OFF — preserves stock behavior. Enable at runtime with the new
    'extgps on' terminal command; the setting persists in flash.
2026-04-30 chore: tag firmware as 4.4.1-extgps for identification
    Adds the '-extgps' suffix to FW_REV so $PAISYS reports
    '4.4.1-extgps' after flashing. Lets users distinguish at runtime
    whether they are running the patched firmware or stock.
    Note: maintainer may prefer to drop this commit before merging
    upstream and tag the version differently. Easy to revert.
